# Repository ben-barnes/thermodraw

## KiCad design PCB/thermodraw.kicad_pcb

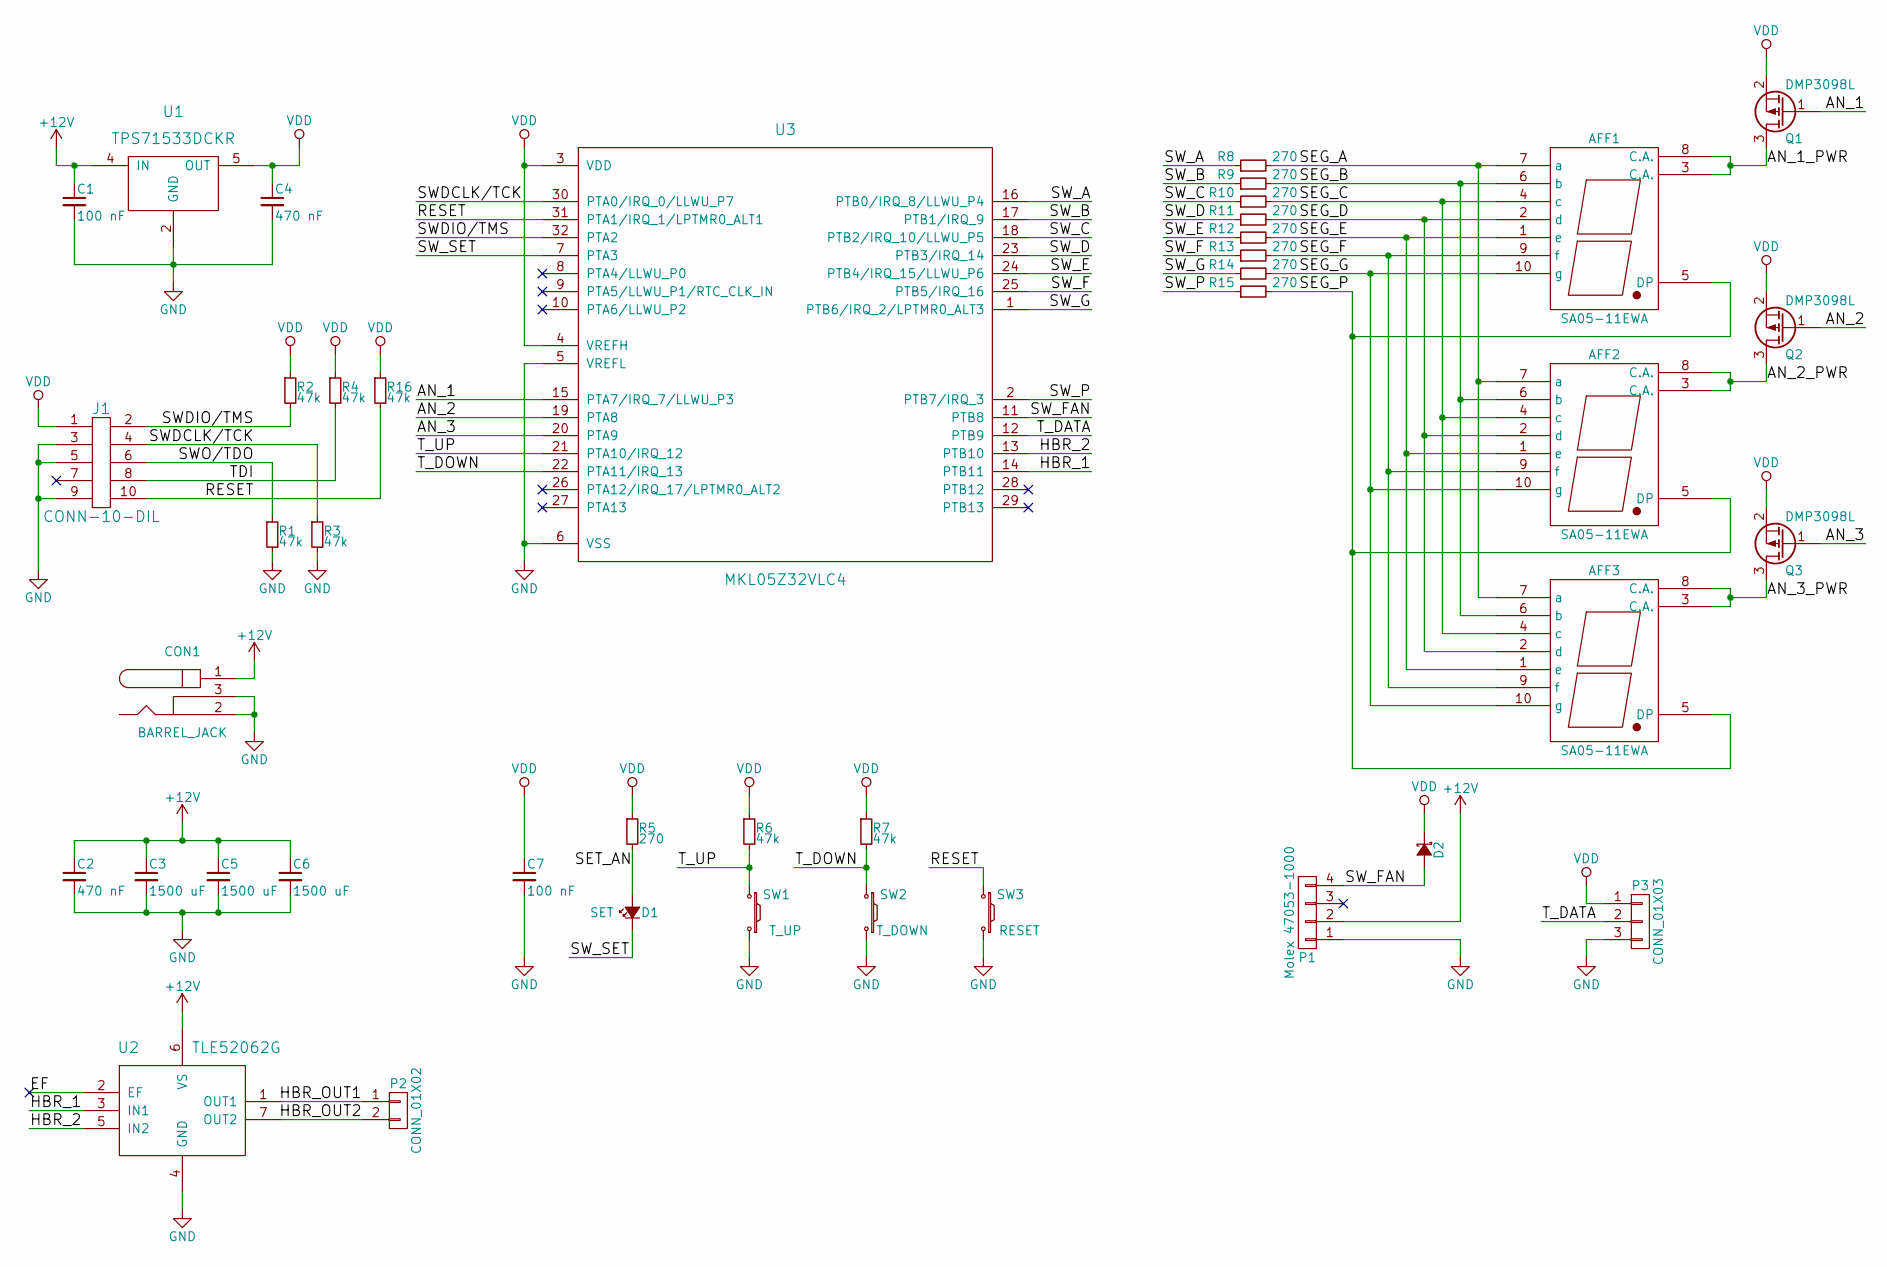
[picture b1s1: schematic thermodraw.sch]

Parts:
AFF1, AFF2, AFF3: SA05-11EWA; 7SegmentLED_LTS6760_LTS6780
C1, C7: 100 nF; C_0603_HandSoldering
C2, C4: 470 nF; C_0603_HandSoldering
C3, C5, C6: 1500 uF; c_elec_18x22; Digikey part no. 1189-3575-2-ND
CON1: BARREL_JACK
D1: SET; LED_0603
D2: CUS520,H3F; SOD-323; Digikey part no. CUS520H3FCT-ND
J1: CONN-10-DIL; Pin_Header_Straight_2x05_Pitch1.27mm
P1: Molex 47053-1000; Molex_KK-6410-04_04x2.54mm_Straight
P2: CONN_01X02; TerminalBlock_Pheonix_MKDS1.5-2pol
P3: CONN_01X03; TerminalBlock_Pheonix_MKDS1.5-3pol
Q1, Q2, Q3: DMP3098L; SOT-23_Handsoldering
R1, R2, R3, R4, R6, R7, R16: 47k; R_0603_HandSoldering
R5, R8, R9, R10, R11, R12, R13, R14, R15: 270; R_0603_HandSoldering
SW1: T_UP; SW_SPST_PTS645; Digikey part no. CKN9087CT-ND
SW2: T_DOWN; SW_SPST_PTS645
SW3: RESET; SW_SPST_PTS645
U1: TPS71533DCKR; SC-70-5
U2: TLE52062G; TO-263-7Lead
U3: MKL05Z32VLC4; LQFP-32_7x7mm_Pitch0.8mm

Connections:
+12V: C1.1, C2.1, C3.1, C5.1, C6.1, CON1.1, P1.2, U1.4 (IN), U2.6 (VS)
/AN_1: Q1.1 (G), U3.15 (PTA7/IRQ_7/LLWU_P3)
/AN_1_PWR: AFF1.3 (C.A.), AFF1.8 (C.A.), Q1.3 (D)
/AN_2: Q2.1 (G), U3.19 (PTA8)
/AN_2_PWR: AFF2.3 (C.A.), AFF2.8 (C.A.), Q2.3 (D)
/AN_3: Q3.1 (G), U3.20 (PTA9)
/AN_3_PWR: AFF3.3 (C.A.), AFF3.8 (C.A.), Q3.3 (D)
/EF: U2.2 (EF)
/HBR_1: U2.3 (IN1), U3.14 (PTB11)
/HBR_2: U2.5 (IN2), U3.13 (PTB10)
/HBR_OUT1: P2.1, U2.1 (OUT1)
/HBR_OUT2: P2.2, U2.7 (OUT2)
/RESET: J1.10, R16.2, SW3.1, U3.31 (PTA1/IRQ_1/LPTMR0_ALT1)
/SEG_A: AFF1.7 (a), AFF2.7 (a), AFF3.7 (a), R8.2
/SEG_B: AFF1.6 (b), AFF2.6 (b), AFF3.6 (b), R9.2
/SEG_C: AFF1.4 (c), AFF2.4 (c), AFF3.4 (c), R10.2
/SEG_D: AFF1.2 (d), AFF2.2 (d), AFF3.2 (d), R11.2
/SEG_E: AFF1.1 (e), AFF2.1 (e), AFF3.1 (e), R12.2
/SEG_F: AFF1.9 (f), AFF2.9 (f), AFF3.9 (f), R13.2
/SEG_G: AFF1.10 (g), AFF2.10 (g), AFF3.10 (g), R14.2
/SEG_P: AFF1.5 (DP), AFF2.5 (DP), AFF3.5 (DP), R15.2
/SET_AN: D1.2 (A), R5.2
/SWDCLK/TCK: J1.4, R3.1, U3.30 (PTA0/IRQ_0/LLWU_P7)
/SWDIO/TMS: J1.2, R2.2, U3.32 (PTA2)
/SWO/TDO: J1.6, R1.1
/SW_A: R8.1, U3.16 (PTB0/IRQ_8/LLWU_P4)
/SW_B: R9.1, U3.17 (PTB1/IRQ_9)
/SW_C: R10.1, U3.18 (PTB2/IRQ_10/LLWU_P5)
/SW_D: R11.1, U3.23 (PTB3/IRQ_14)
/SW_E: R12.1, U3.24 (PTB4/IRQ_15/LLWU_P6)
/SW_F: R13.1, U3.25 (PTB5/IRQ_16)
/SW_FAN: D2.2 (A), P1.4, U3.11 (PTB8)
/SW_G: R14.1, U3.1 (PTB6/IRQ_2/LPTMR0_ALT3)
/SW_P: R15.1, U3.2 (PTB7/IRQ_3)
/SW_SET: D1.1 (K), U3.7 (PTA3)
/TDI: J1.8, R4.2
/T_DATA: P3.2, U3.12 (PTB9)
/T_DOWN: R7.2, SW2.1, U3.22 (PTA11/IRQ_13)
/T_UP: R6.2, SW1.1, U3.21 (PTA10/IRQ_12)
GND: C1.2, C2.2, C3.2, C4.2, C5.2, C6.2, C7.2, CON1.2, CON1.3, J1.3, J1.5, J1.9, P1.1, P3.3, R1.2, R3.2, SW1.2, SW2.2, SW3.2, U1.2 (GND), U2.4 (GND), U3.5 (VREFL), U3.6 (VSS)
VDD: C4.1, C7.1, D2.1 (K), J1.1, P3.1, Q1.2 (S), Q2.2 (S), Q3.2 (S), R2.1, R4.1, R5.1, R6.1, R7.1, R16.1, U1.5 (OUT), U3.3 (VDD), U3.4 (VREFH)

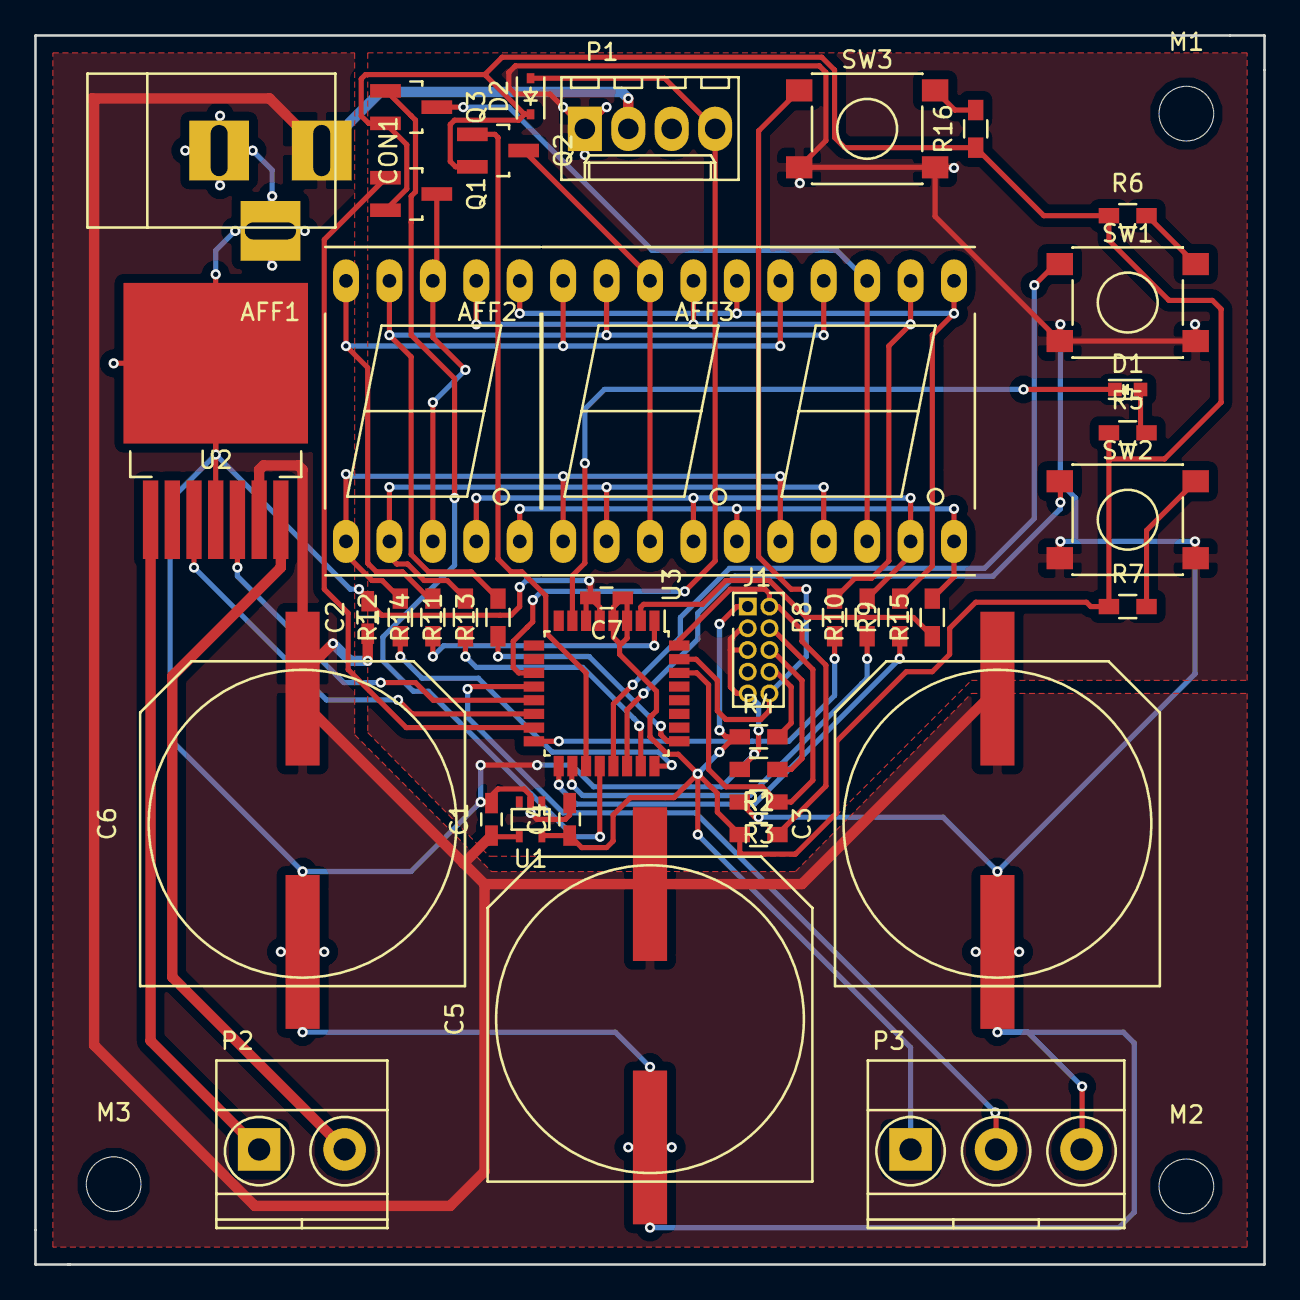
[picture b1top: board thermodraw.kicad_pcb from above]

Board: 2 copper layers, 71.9 x 71.9 mm, 45 parts (0 on the bottom side), 40 nets.

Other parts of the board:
M1, M2, M3: MountingHole_3.2mm_M3

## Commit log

2017-01-26 Initial commit.
2017-01-26 Added capacitor footprints.
2017-01-31 Finished routing, added pours.
